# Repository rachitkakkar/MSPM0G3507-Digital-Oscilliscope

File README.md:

# MSPM0G3507 Digital Storage Oscilloscope

This repository contains the firmware for an Digital Storage Oscilloscope, developed for the Texas Instruments **MSPM0G3507** microcontroller. The project leverages interrupt-driven sampling, real-time graphics rendering to an ST7735 TFT LCD display, and interactive peripherals on a custom PCB designed in KiCAD.

*Low quality GIF displaying oscilloscope at different frequencies*

*Low quality GIF displaying scope at different zoom levels (controlled via slide pot)*

## Features

- **High-Speed Signal Acquisition**: There is a 50 kHz hardware timer interrupt (TimerG6) to sample the ADC and store the value in a storage buffer. The process of sampling and storing into the buffer only occurs on the rising edge of the signal after it passes a trigger set at the half-way mark in order to capture stable waveforms.
- **Real-Time Display**: Live waveform plotting on an ST7735 TFT LCD with grid generation and zoom. Displaying the waveform only occurs when the buffer is full, upon which the 50 kHz TimerG6 interrupt is disabled in order to plot values onto the LCD. Without this crucial step, the microcontroller would be interrupted before it had time to write to the display as that is a comparatively slow task relative to the frequent timer interrupts. In order to further speed up the display (and prevent the flickering of a whole screen redraw), a buffer of previous samples is stored and only the pixels of the previous waveform are cleared. This also requires dynamically fixing the grid in those spots.
- **Interactive Measurements**: 
  - Dual horizontal and vertical cursors to measure $\Delta V$, $\Delta T$.
  - Real-time on-screen calculations for Peak-to-Peak Voltage ($V_{pp}$) and Frequency.
- **Dynamic Controls**:
  - Discrete zoom levels (1x, 2x, 4x) controlled by an ADC-sampled slide potentiometer and downsampling of the ADC sample buffer.
  - Hardware switch integration for playback control (Play/Pause), cursor selection, and precise cursor movement.
  - Input control is handled by another periodic hardware timer interrupt (TimerG12), this time at a frequency of only 30 Hz.
- **Audio Feedback**: DAC-driven sound generation mapped to UI interactions for tactile and auditory feedback. The audio files are downsampled and stored into a C array, where a periodic SysTick interrupt then outputs the values to the 5-bit DAC on the PCB at a frequency of 11 kHz. To prevent noticeable audio distortion, this interrupt is the highest priority.
- **Localization**: Built-in dual-language support (English and Spanish) for the on-screen display.
- **Debugging**: LED based triple toggle to determine latency of interrupt handler.

## Architecture and Key Components

- **`Lab9HMain.cpp`**: The primary entry point. Registers the 30 Hz UI/Game engine timer interrupt, the 50 kHz ADC sampling timer interrupt, the 11 kHz SysTick interrupt, and the main application loop. Also stores code for the corresponding IRQ handlers.
- **`Oscilloscope.cpp` / `.h`**: Core oscilloscope logic. Handles ADC configuration, sample buffering, trigger-level synchronization, and signal metrics calculations (Frequency, $V_{pp}$).
- **`ST7735.cpp` / `.h`**: Display driver for the SPI-based LCD, including routines for drawing bitmaps, characters, and primitive shapes.
- **`Cursor` & `Application`**: Encapsulates the UI state, grid drawing, and cursor boundary/overlap logic.
- **Peripherals**: Interfaces for `Clock`, `Timer`, `Switch`, `SlidePot`, `LED`, `Sound`, and `DAC5`.

## Hardware

- **Microcontroller**: TI MSPM0G3507 LaunchPad
- **Display**: ST7735 SPI LCD (Adafruit REDTAB or HiLetGo BLACKTAB)
- **Inputs**: 
  - Slide Potentiometer (ADC input)
  - 4 Tactile Switches (Digital GPIO)
- **Outputs**: 
  - 5-bit weighted DAC, amplifier chip, and speaker (for audio)
  - LEDs (triple toggle and pause indicator)

The full PCB files are available in the `PCB/` folder

## Build Instructions

This project is built using Code Composer Studio (CCS) and the TI MSPM0-SDK. 

1. Import the project folder into a Code Composer Studio workspace.
2. Ensure the `MSPM0-SDK` (v2.9.0.01 or compatible) and SysConfig are correctly linked in your project properties.
3. Build the project using the **TI Arm Clang Compiler** (`TICLANG`).
4. Flash the `.out` executable onto the MSPM0G3507 LaunchPad.

## Credits

Much of the starter code for this project was developed by the instructors for ECE319H Course at the University of Texas at Austin.

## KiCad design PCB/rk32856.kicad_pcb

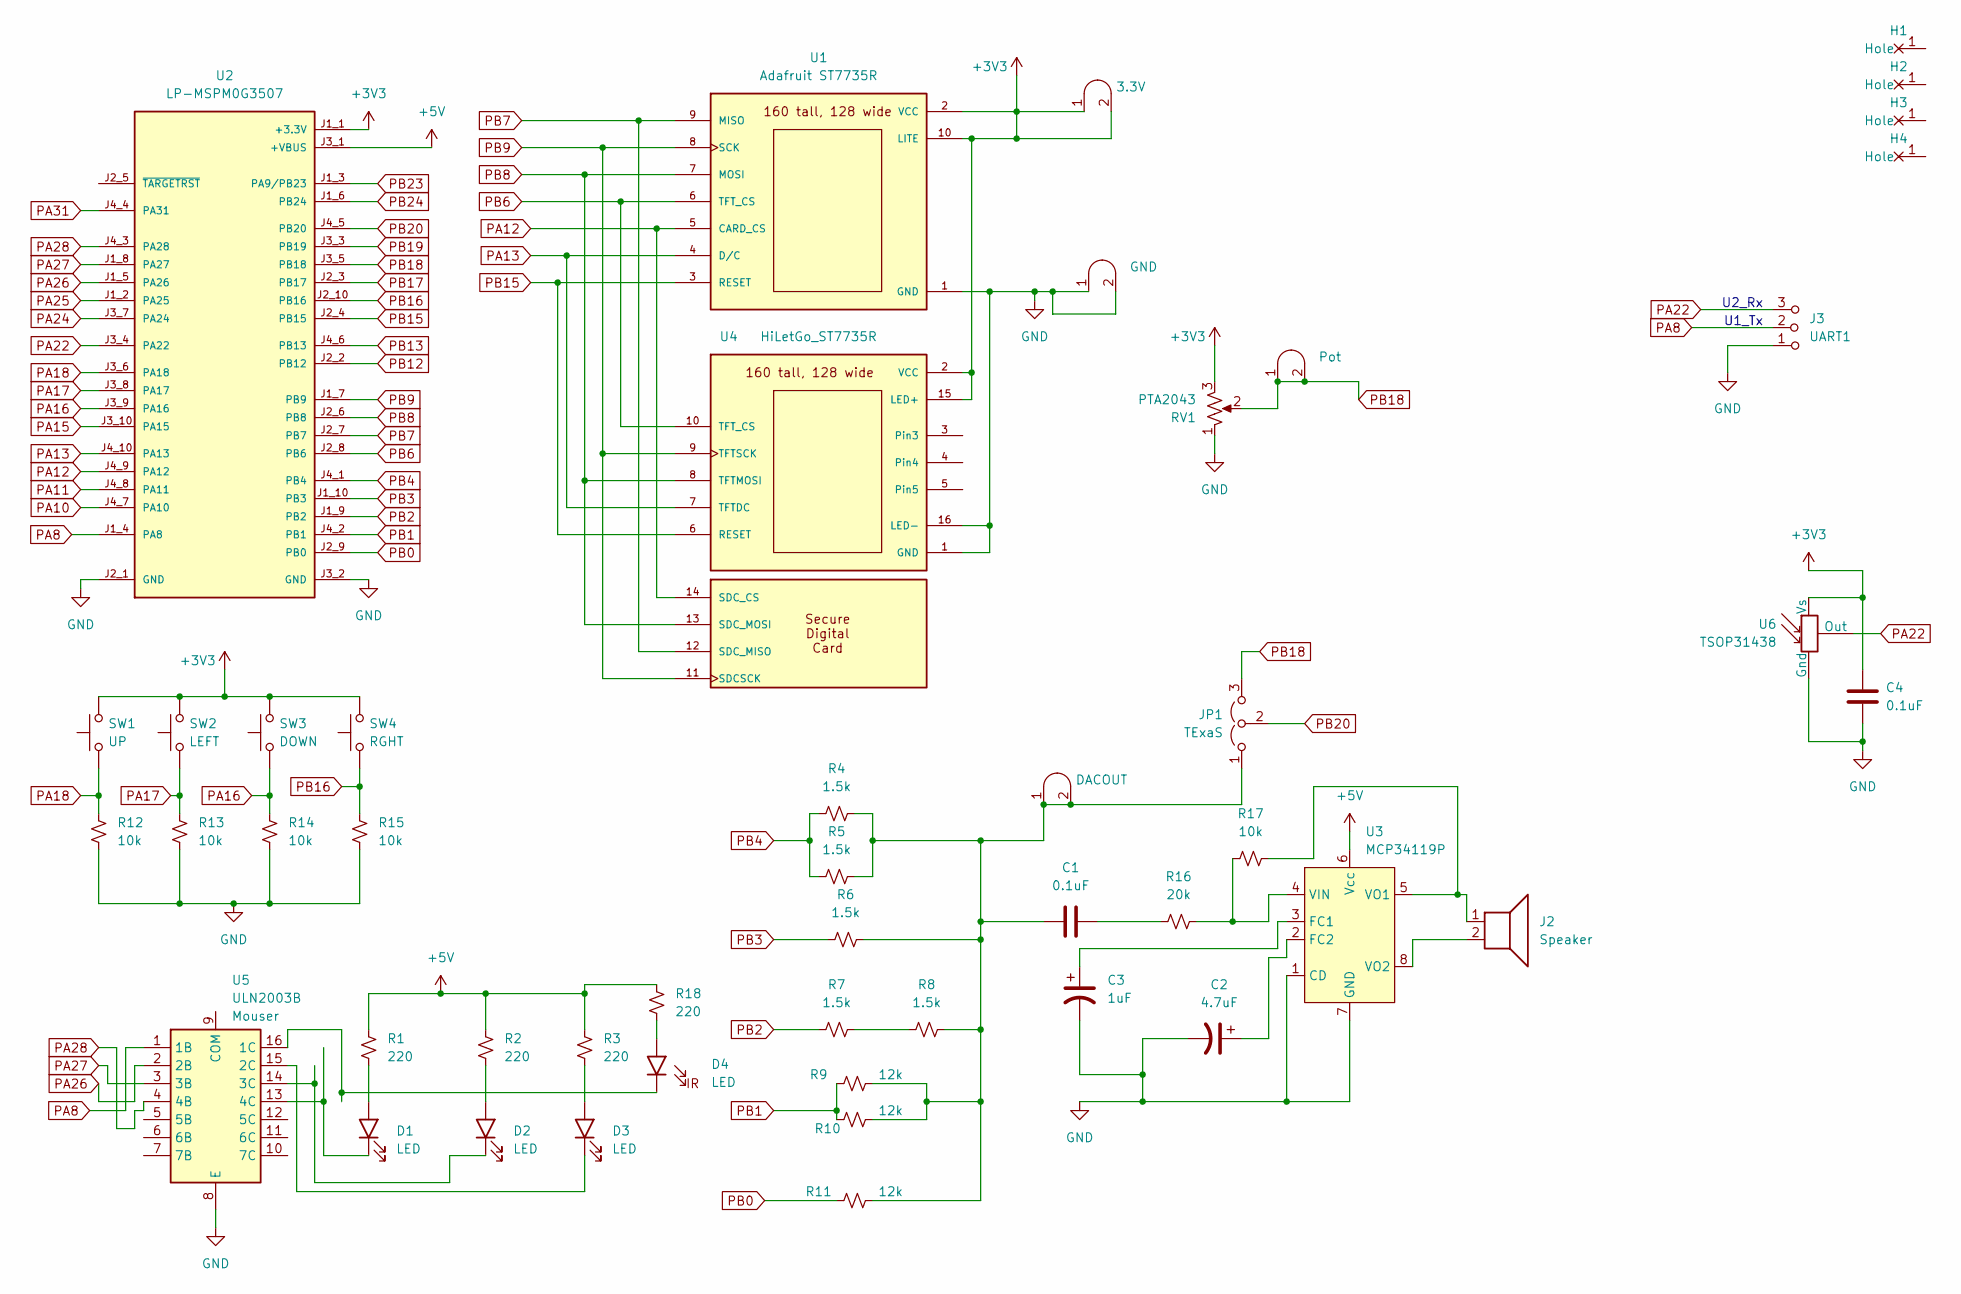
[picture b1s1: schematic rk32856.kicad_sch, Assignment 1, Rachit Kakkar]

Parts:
C1, C4: 0.1uF; C_Axial_200mil
C2: 4.7uF; CP_Radial_Tantal200mil
C3: 1uF; CP_Radial_Tantal200mil
D1, D2, D3, D4: LED; LED_D5.0mm
H1, H2, H3, H4: MountingHole_4_40
J2: Speaker; PinHeader_1x02_P2.54mm_Vertical
J3: UART1; PinHeader_1x03_P2.54mm_Vertical
J4: Pot; Testpoint_1x02_P2.54mm
J6: GND; Testpoint_1x02_P2.54mm
J7: DACOUT; Testpoint_1x02_P2.54mm
JP1: TExaS; PinHeader_1x03_P2.54mm_Vertical
R1, R2, R3, R18: 220; R_Axial_DIN0204_L3.6mm_D1.6mm_P7.62mm_Horizontal
R4, R5, R6, R7, R8: 1.5k; R_Axial_DIN0204_L3.6mm_D1.6mm_P7.62mm_Horizontal
R9, R10, R11: 12k; R_Axial_DIN0204_L3.6mm_D1.6mm_P7.62mm_Horizontal
R12, R13, R14, R15, R17: 10k; R_Axial_DIN0204_L3.6mm_D1.6mm_P7.62mm_Horizontal
R16: 20k; R_Axial_DIN0204_L3.6mm_D1.6mm_P7.62mm_Horizontal
RV1: PTA2043; PTA2043pot
SW1: UP; SW_PUSH_6mm
SW2: LEFT; SW_PUSH_6mm
SW3: DOWN; SW_PUSH_6mm
SW4: RGHT; SW_PUSH_6mm
TP1: 3.3V; Testpoint_1x02_P2.54mm
U1: Adafruit ST7735R; adafruit_st7735r
U2: LP-MSPM0G3507; ti_LP_MSPM0G3507
U3: MCP34119P; DIP-8_W7.62mm_LongPads
U4: HiLetGo_ST7735R; hiletgo_st7735r
U5: ULN2003B; DIP-16_W7.62mm
U6: TSOP31438

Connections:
+3V3: C4.1, RV1.3, SW1.2, SW2.2, SW3.2, SW4.2, TP1.1 (A), TP1.2 (B), U1.2 (VCC), U1.10 (LITE), U2.J1_1 (+3.3V), U4.2 (VCC), U4.15 (LED+), U6.2 (Vs)
+5V: R1.1, R2.1, R3.1, R18.1, U2.J3_1 (+VBUS), U3.6 (Vcc)
GND: C2.2, C3.2, C4.2, J3.1 (A), J6.1 (A), J6.2 (B), R12.2, R13.2, R14.2, R15.2, RV1.1, U1.1 (GND), U2.J2_1 (GND), U2.J3_2 (GND), U3.1 (CD), U3.7 (GND), U4.1 (GND), U4.16 (LED-), U5.8 (E), U6.1 (Gnd)
unnamed: C1.2, R16.1
unnamed: D1.2 (A), R1.2
unnamed: D1.1 (K), U5.13 (4C)
unnamed: D2.2 (A), R2.2
unnamed: D2.1 (K), U5.14 (3C)
unnamed: D3.2 (A), R3.2
unnamed: D3.1 (K), U5.15 (2C)
unnamed 10: D4.2 (A), R18.2; also elsewhere on the board
unnamed 11: D4.1 (K), U5.16 (1C); also elsewhere on the board
unnamed: C1.1, J7.1 (A), J7.2 (B), JP1.1 (A), R4.1, R5.1, R6.1, R8.1, R9.1, R10.1, R11.1
unnamed: R7.1, R8.2
unnamed: C3.1, U3.3 (FC1)
unnamed: C2.1, U3.2 (FC2)
unnamed: R16.2, R17.1, U3.4 (VIN)
unnamed: J2.1, R17.2, U3.5 (VO1)
unnamed: J2.2, U3.8 (VO2)
PA8: J3.2 (B), U2.J1_4 (PA8), U5.1 (1B)
PA10: U2.J4_7 (PA10)
PA11: U2.J4_8 (PA11)
PA12: U1.5 (CARD_CS), U2.J4_9 (PA12), U4.14 (SDC_CS)
PA13: U1.4 (D/C), U2.J4_10 (PA13), U4.7 (TFTDC)
PA15: U2.J3_10 (PA15)
PA16: R14.1, SW3.1, U2.J3_9 (PA16)
PA17: R13.1, SW2.1, U2.J3_8 (PA17)
PA18: R12.1, SW1.1, U2.J3_6 (PA18)
PA22: J3.3 (C), U2.J3_4 (PA22), U6.3 (Out)
PA24: U2.J3_7 (PA24)
PA25: U2.J1_2 (PA25)
PA26: U2.J1_5 (PA26), U5.2 (2B)
PA27: U2.J1_8 (PA27), U5.3 (3B)
PA28: U2.J4_3 (PA28), U5.4 (4B)
PA31: U2.J4_4 (PA31)
PB0: R11.2, U2.J2_9 (PB0)
PB1: R9.2, R10.2, U2.J4_2 (PB1)
PB2: R7.2, U2.J1_9 (PB2)
PB3: R6.2, U2.J1_10 (PB3)
PB4: R4.2, R5.2, U2.J4_1 (PB4)
PB6: U1.6 (TFT_CS), U2.J2_8 (PB6), U4.10 (TFT_CS)
PB7: U1.9 (MISO), U2.J2_7 (PB7), U4.12 (SDC_MISO)
PB8: U1.7 (MOSI), U2.J2_6 (PB8), U4.8 (TFTMOSI), U4.13 (SDC_MOSI)
PB9: U1.8 (SCK), U2.J1_7 (PB9), U4.9 (TFTSCK), U4.11 (SDCSCK)
PB12: U2.J2_2 (PB12)
PB13: U2.J4_6 (PB13)
PB15: U1.3 (RESET), U2.J2_4 (PB15), U4.6 (RESET)
PB16: R15.1, SW4.1, U2.J2_10 (PB16)
PB17: U2.J2_3 (PB17)
PB18: J4.1 (A), J4.2 (B), JP1.3 (B), RV1.2, U2.J3_5 (PB18)
PB19: U2.J3_3 (PB19)
PB20: JP1.2 (C), U2.J4_5 (PB20)
PB23: U2.J1_3 (PA9/PB23)
PB24: U2.J1_6 (PB24)

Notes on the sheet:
U2_Rx
U1_Tx

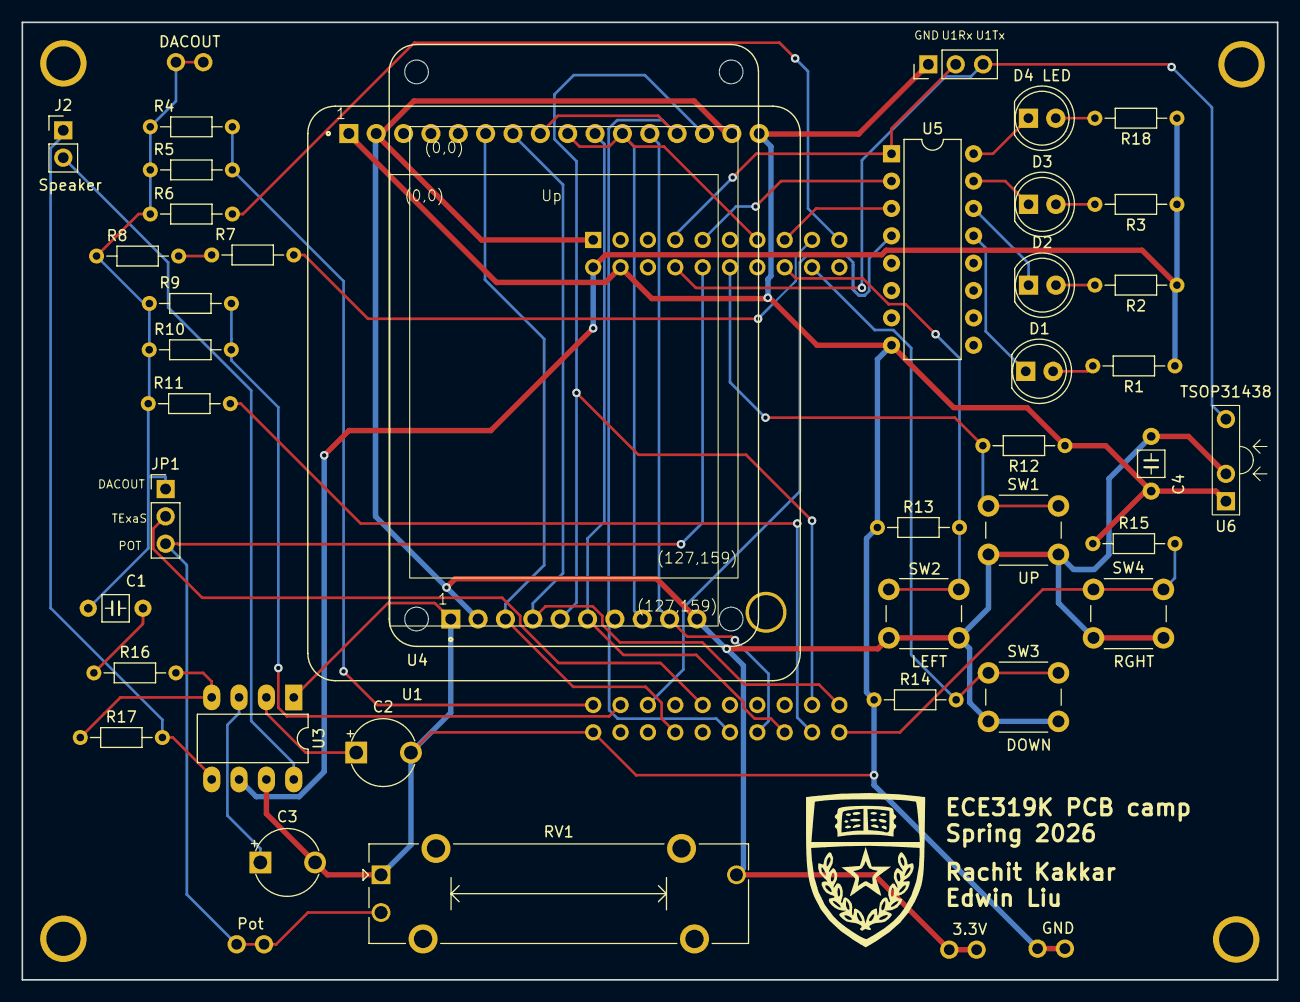
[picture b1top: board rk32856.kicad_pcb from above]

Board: 2 copper layers, 116.5 x 88.9 mm, 48 parts (1 on the bottom side), 42 nets.

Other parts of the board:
D4 LED: LED; LED_D5.0mm

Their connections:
unnamed 10: D4 LED.2 (A); also elsewhere on the board
unnamed 11: D4 LED.1 (K); also elsewhere on the board

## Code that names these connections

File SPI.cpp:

/* SPI.cpp
 * Jonathan Valvano
 * November 21, 2022
 * Derived from uart_rw_multibyte_fifo_poll_LP_MSPM0G3507_nortos_ticlang
SPI MKII LCD
J1.7  SPI1 SCLK  PB9_SPI1-SCK
J2.13 SPI1 CS0   PB6_SPI1-CS0
J2.15 SPI1 PICO  PB8_SPI1-PICO
J2.17 LCD !RST   PB15
J4.31 LCD RS     PA13
 */


#include <ti/devices/msp/msp.h>
#include "SPI.h"
#include "Clock.h"
#define PB9INDEX 25
#define PB6INDEX 22
#define PB8INDEX 24
#define PB15INDEX 31
#define PA13INDEX 34
// calls Clock_Freq to get bus clock
// initialize SPI for 8 MHz baud clock
// busy-wait synchronization
// SPI0,SPI1 in power domain PD1 SysClk equals bus CPU clock
void SPI_Init(void){uint32_t busfreq =  Clock_Freq();
    // assumes GPIOA and GPIOB are reset and powered previously
    // RSTCLR to SPI1 peripherals
    //   bits 31-24 unlock key 0xB1
    //   bit 1 is Clear reset sticky bit
    //   bit 0 is reset gpio port
  SPI1->GPRCM.RSTCTL = 0xB1000003;
    // Enable power to SPI1 peripherals
    // PWREN
    //   bits 31-24 unlock key 0x26
    //   bit 0 is Enable Power
  SPI1->GPRCM.PWREN = 0x26000001;
  // configure PB9 PB6 PB8 as alternate SPI1 function
  IOMUX->SECCFG.PINCM[PB9INDEX]  = 0x00000083;  // SPI1 SCLK
  IOMUX->SECCFG.PINCM[PB6INDEX]  = 0x00000083;  // SPI1 CS0
  IOMUX->SECCFG.PINCM[PB8INDEX]  = 0x00000083;  // SPI1 PICO
  IOMUX->SECCFG.PINCM[PB15INDEX] = 0x00000081;  // GPIO output, LCD !RST
  IOMUX->SECCFG.PINCM[PA13INDEX] = 0x00000081;  // GPIO output, LCD RS
  Clock_Delay(24); // time for gpio to power up
  GPIOA->DOE31_0 |= 1<<13;    // PA13 is LCD RS
  GPIOB->DOE31_0 |= 1<<15;    // PB15 is LCD !RST
  GPIOA->DOUTSET31_0 = 1<<13; // RS=1
  GPIOB->DOUTSET31_0 = 1<<15; // !RST = 1
  SPI1->CLKSEL = 8; // SYSCLK
// bit 3 SYSCLK
// bit 2 MFCLK
// bit 1 LFCLK
   SPI1->CLKDIV = 0; // divide by 1
// bits 2-0 n (0 to 7), divide by n+1
//Set the bit rate clock divider to generate the serial output clock
//     outputBitRate = (spiInputClock) / ((1 + SCR) * 2)
//     8,000,000 = (16,000,000)/((0 + 1) * 2)
//     8,000,000 = (32,000,000)/((1 + 1) * 2)
//     6,666,667 = (40,000,000)/((2 + 1) * 2)
//    10,000,000 = (40,000,000)/((1 + 1) * 2)
//     8,000,000 = (80,000,000)/((4 + 1) * 2)
//     8,000,000 = (Clock_Freq)/((m + 1) * 2)
//     m = (Clock_Freq/16000000) - 1
   if(busfreq <= 16000000){
     SPI1->CLKCTL = 0; // frequency= busfreq/2
   }else if(busfreq == 40000000){
     SPI1->CLKCTL = 1; // frequency= 10MHz
    // SPI1->CLKCTL = 2; // frequency= 6.66MHz
   }else{
     SPI1->CLKCTL = busfreq/16000000 -1; // 8 MHz
   }
   SPI1->CTL0 = 0x0027;
// bit 14 CSCLR=0 not cleared
// bits 13-12 CSSEL=0 CS0
// bit 9 SPH = 0
// bit 8 SPO = 0
// bits 6-5 FRF = 01 (4 wire)
// bits 4-0 n=7, data size is n+1 (8bit data)
  SPI1->CTL1 = 0x0015;
// bits 29-24 RXTIMEOUT=0
// bits 23-16 REPEATX=0 disabled
// bits 15-12 CDMODE=0 manual
// bit 11 CDENABLE=0 CS3
// bit 7-5 =0 no parity
// bit 4=1 MSB first
// bit 3=0 POD (not used, not peripheral)
// bit 2=1 CP controller mode
// bit 1=0 LBM disable loop back
// bit 0=1 enable SPI
  SPI_Reset();
}
/* STAT register
 * 4 BUSY 0h = SPI is in idle mode. 1h = SPI is currently transmitting and/or receiving data, or transmit FIFO is not empty.
   3 RNF Receive FIFO not full 0h = Receive FIFO is full. 1h = Receive FIFO is not full.
   2 RFE Receive FIFO empty. 0h = Receive FIFO is not empty. 1h = Receive FIFO is empty.
   1 TNF Transmit FIFO not full 0h = Transmit FIFO is full. 1h = Transmit FIFO is not full.
   0 TFE Transmit FIFO empty. 0h = Transmit FIFO is not empty. 1h = Transmit FIFO is empty.*/

//---------SPI_OutData------------
// Output 8-bit data to SPI port
// Input: data is an 8-bit data to be transferred
// Output: none
void SPI_OutData(char data){
  while((SPI1->STAT&0x02) == 0x00){}; // spin if TxFifo full
  GPIOA->DOUTSET31_0 = 1<<13;         // RS=PA13=1 for data
  SPI1->TXDATA = data;
}
 //---------SPI_OutCommand------------
 // Output 8-bit command to SPI port
 // Input: data is an 8-bit data to be transferred
 // Output: none
 void SPI_OutCommand(char command){
   while((SPI1->STAT&0x10) == 0x10){}; // spin if SPI busy
   GPIOA->DOUTCLR31_0 = 1<<13;         // RS=PA13=0 for command
   SPI1->TXDATA = command;
   while((SPI1->STAT&0x10) == 0x10){}; // spin if SPI busy
 }

 //---------SPI_Reset------------
 // Reset LCD
 // Input: none
 // Output: none
 // at 48 MHz
 void SPI_Reset(void){
   GPIOB->DOUTSET31_0 = 1<<15; // PB15=!RST=1
   Clock_Delay1ms(500);        // 500ms (calibrated with logic analyzer)
   GPIOB->DOUTCLR31_0 = 1<<15; // PB15=!RST=0
   Clock_Delay1ms(500);        // 500ms
   GPIOB->DOUTSET31_0 = 1<<15; // PB15=!RST=1
   Clock_Delay1ms(500);        // 500ms
 }

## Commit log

2026-04-13 Add inital sampling of ADC (10kHz timer interrupt) and plotting to LCD grid
2026-04-17 Get oscilliscope to fully work for signals up to 100 Hz, start horizontal measurement cursors
2026-04-20 rachit is awesome
2026-04-21 Fix grid line issue
2026-04-21 rachit is the goat
2026-04-21 Shayaan is the goat
2026-04-21 Frequency mostly works, also add option for user to clear screen and avoid artificating
2026-04-23 Add zoom, frequency, vpp, and cursor information. Also add support for spanish and integrate cursor overlap code.
2026-05-13 Remove all linked resources and include them in project / Git tracking
2026-05-14 Add an extensive README and perform minor code clean-up
2026-05-14 Add another demo gif and run README through spell check
2026-05-14 And with removing that piece of clunky english, I have finally completed the READMEs for all my old projects....
